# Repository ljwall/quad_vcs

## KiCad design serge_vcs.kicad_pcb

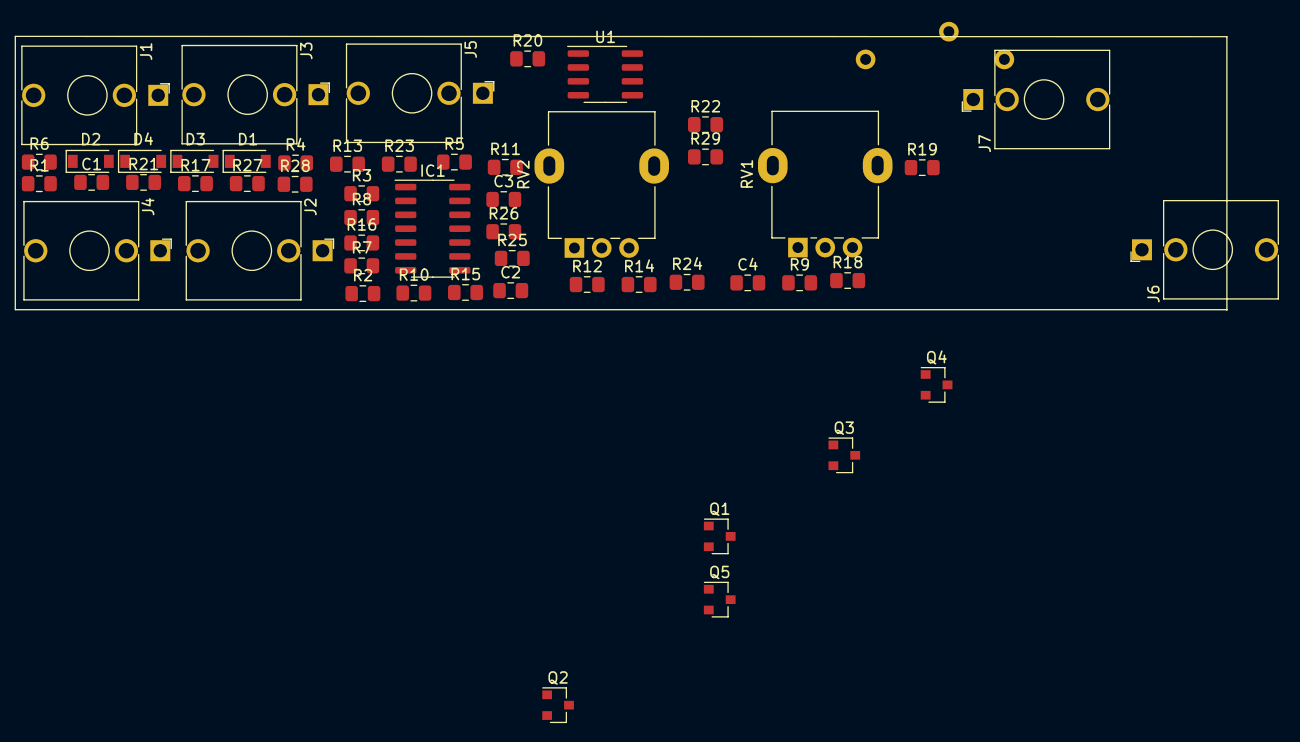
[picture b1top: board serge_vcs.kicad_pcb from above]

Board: 2 copper layers, 54 parts (1 on the bottom side), 38 nets, no tracks yet.

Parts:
C1: 1n; C_0805_2012Metric_Pad1.15x1.40mm_HandSolder
C2, C3: 47p; C_0805_2012Metric_Pad1.15x1.40mm_HandSolder
C4: 22n; C_0805_2012Metric_Pad1.15x1.40mm_HandSolder
D1, D2, D3: 1N4148; D_SOD-123
D4: 5v6 (test current 5mA); D_SOD-123
IC1: LM3900; SOIC-14_3.9x8.7mm_P1.27mm
J1: Trigger; Jack_3.5mm_QingPu_WQP-PJ398SM_Vertical_CircularHoles
J2: Fall CV; Jack_3.5mm_QingPu_WQP-PJ398SM_Vertical_CircularHoles
J3: Rise CV; Jack_3.5mm_QingPu_WQP-PJ398SM_Vertical_CircularHoles
J4: Input; Jack_3.5mm_QingPu_WQP-PJ398SM_Vertical_CircularHoles
J5: 1v/Oct; Jack_3.5mm_QingPu_WQP-PJ398SM_Vertical_CircularHoles
J6: End out; Jack_3.5mm_QingPu_WQP-PJ398SM_Vertical_CircularHoles
J7: DC Output; Jack_3.5mm_QingPu_WQP-PJ398SM_Vertical_CircularHoles
Q1, Q4: 2N3904; SOT-23
Q2, Q3, Q5: 2N3906; SOT-23
R1, R2, R13, R15: 100k; R_0805_2012Metric_Pad1.15x1.40mm_HandSolder
R3: 33k; R_0805_2012Metric_Pad1.15x1.40mm_HandSolder
R4, R5, R6, R7, R14: 82k; R_0805_2012Metric_Pad1.15x1.40mm_HandSolder
R8, R9: 2k2; R_0805_2012Metric_Pad1.15x1.40mm_HandSolder
R10, R11: 820k; R_0805_2012Metric_Pad1.15x1.40mm_HandSolder
R12, R23, R24, R29: 220k; R_0805_2012Metric_Pad1.15x1.40mm_HandSolder
R16: 1k8; R_0805_2012Metric_Pad1.15x1.40mm_HandSolder
R17, R21: 1M; R_0805_2012Metric_Pad1.15x1.40mm_HandSolder
R18, R22: 10M; R_0805_2012Metric_Pad1.15x1.40mm_HandSolder
R19: 8k2; R_0805_2012Metric_Pad1.15x1.40mm_HandSolder
R20: 330k; R_0805_2012Metric_Pad1.15x1.40mm_HandSolder
R25: 68k; R_0805_2012Metric_Pad1.15x1.40mm_HandSolder
R26: 100R; R_0805_2012Metric_Pad1.15x1.40mm_HandSolder
R27: 1k2; R_0805_2012Metric_Pad1.15x1.40mm_HandSolder
R28: 1k; R_0805_2012Metric_Pad1.15x1.40mm_HandSolder
RV1, RV2: B50k; Potentiometer_Alpha_RD901F-40-00D_Single_Vertical
RV3: 100k trim; Potentiometer_Bourns_3005_Horizontal
U1: TL072; SOIC-8_3.9x4.9mm_P1.27mm

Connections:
+12V: IC1.14, Q5.1, R22.2, R25.2, RV1.1, RV2.1, U1.8
-12V: R29.1, U1.4
/Attack: IC1.5, R11.2, R23.2
/EOC: D2.1, IC1.9, R17.1, R21.2, R27.2
/EndofRise: C2.2, IC1.4, R10.1
/FALL_CTRL: Q3.2, R4.1, R5.1, R8.1
/Out: J7.T, R20.2, R26.1, RV3.1
/RISE_CTRL: Q1.2, R6.1, R7.1, R9.1
GND: D4.2, IC1.7, IC1.12, J1.S, J1.TN, J2.S, J2.TN, J3.S, J3.TN, J4.S, J4.TN, J5.S, J5.TN, J6.S, J7.S, J7.TN, Q1.3, Q2.3, R1.1, R2.1, R8.2, R9.2, R13.1, R16.1, RV1.3, RV2.3, RV3.3, U1.3
unnamed: C1.1, J1.T, R1.2
unnamed: C1.2, R2.2, R3.2
unnamed: C2.1, IC1.6, R10.2
unnamed: C3.1, R15.1, U1.6
unnamed: C3.2, R18.2
unnamed: C4.1, Q3.3, Q4.3, U1.2
unnamed: C4.2, R24.1, R26.2, U1.1
unnamed: D1.1, IC1.1
unnamed: D1.2, D2.2, R3.1
unnamed: D3.1, Q5.3, R29.2
unnamed: D3.2, R24.2, U1.5
unnamed: D4.1, R27.1, R28.1
unnamed: IC1.2, R12.2
unnamed: IC1.3, R11.1
unnamed: IC1.8, R20.1, R22.1
unnamed: IC1.11, R17.2
unnamed: IC1.13, R21.1
unnamed: J2.T, R5.2
unnamed: J3.T, R7.2
unnamed: J4.T, R13.2, R15.2
unnamed: J5.T, R14.2
unnamed: J6.T, R28.2
unnamed: Q1.1, Q2.1, Q3.1, Q4.1, R19.2
unnamed: Q2.2, Q4.2, R14.1, R16.2
unnamed: Q5.2, R23.1, R25.1
unnamed: R4.2, RV1.2
unnamed: R6.2, RV2.2
unnamed: R12.1, RV3.2
unnamed: R18.1, R19.1, U1.7
